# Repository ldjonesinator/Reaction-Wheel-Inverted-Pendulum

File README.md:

# Reaction Wheel Inverted Pendulum

## How it works
An inverted pendulum is an inherently unstable mechanical system because its centre of mass is positioned above its pivot point. As a result, small disturbances cause the pendulum to move away from its upright position unless corrected back to its original position. In this project, torque is produced by accelerating or decelerating a reaction wheel mounted to the pendulum. The resulting reaction torque acts on the pendulum body and is used to oppose its movement. 

The design uses an inertial measurement unit (IMU), to measure the pendulum’s angular position and motion. These measurements are processed by a Raspberry Pi Pico, which runs the feedback-control algorithm. The resulting control signal is supplied to an H-bridge motor driver, allowing the speed and direction of the brushed geared DC motor to be controlled. The motor drives the reaction wheel, completing the closed-loop control system. 

## How to use
You can refer to the documentation located in: [Instructions](Instructions.pdf)

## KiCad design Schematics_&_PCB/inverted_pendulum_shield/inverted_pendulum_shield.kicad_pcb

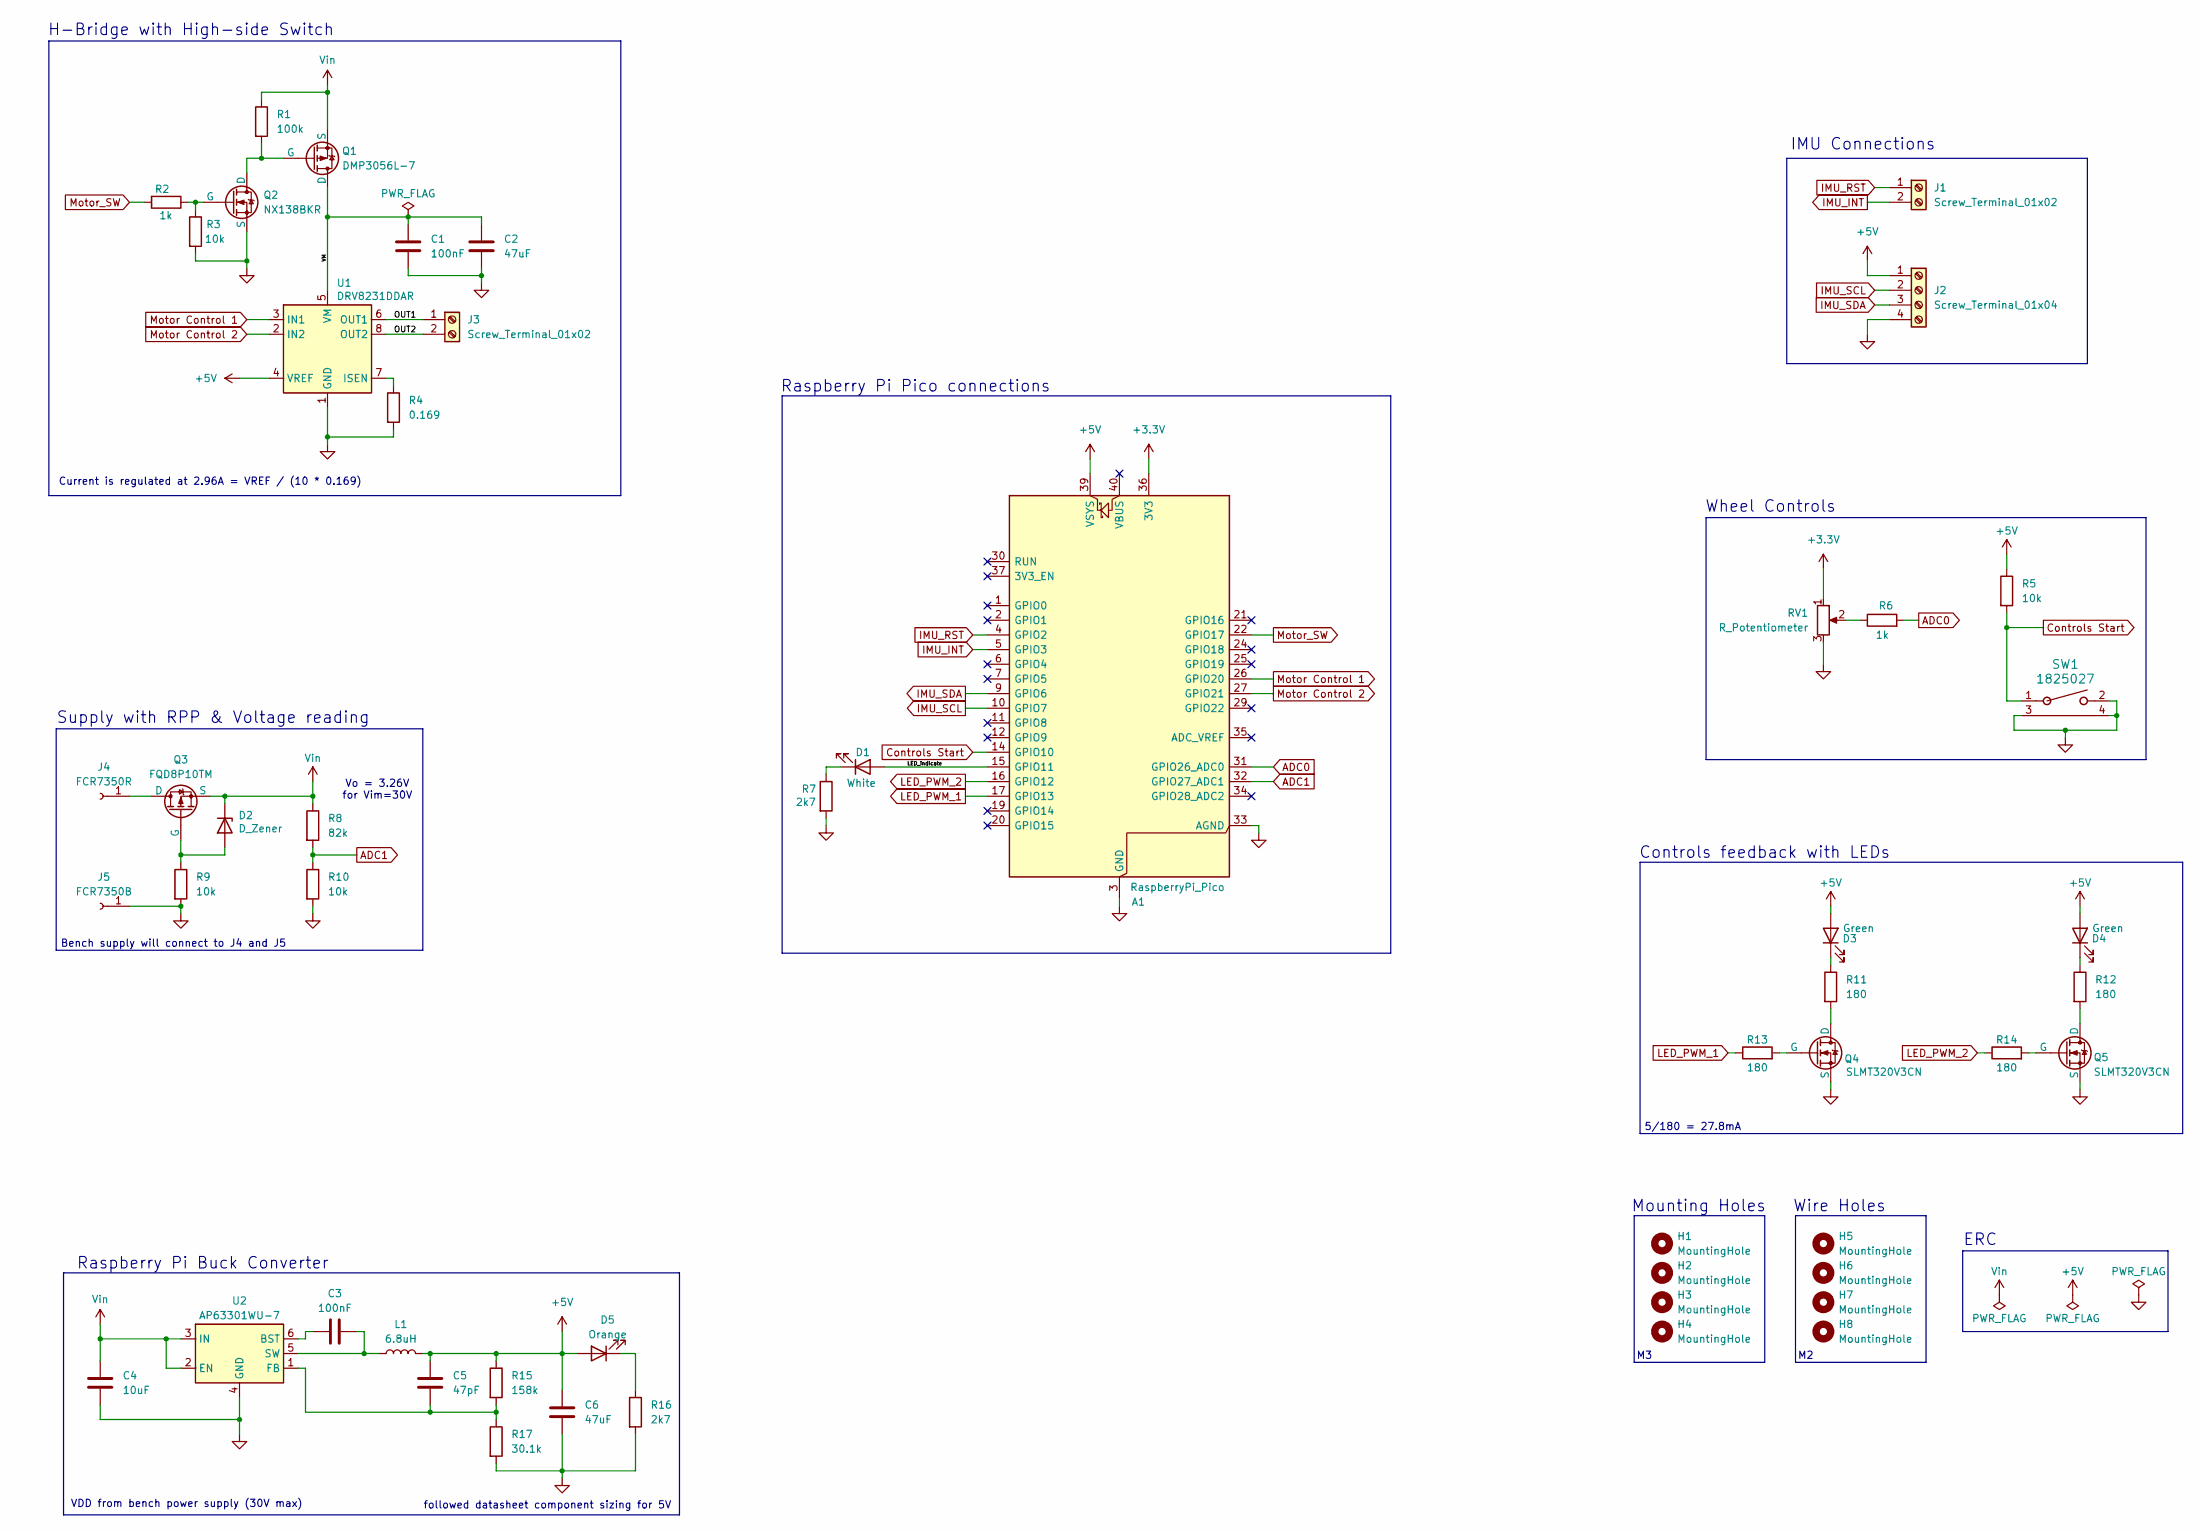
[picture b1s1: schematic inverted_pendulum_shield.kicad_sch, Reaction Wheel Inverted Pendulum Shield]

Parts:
A1: RaspberryPi_Pico; RaspberryPi_Pico_Common_THT
C1, C3: 100nF; C_0805_2012Metric
C2: 47uF; C_Radial_D5.0mm_H11.0mm_P2.00mm
C4: 10uF; C_0805_2012Metric
C5: 47pF; C_0603_1608Metric
C6: 47uF; C_0805_2012Metric
D1: White; LED_0603_1608Metric
D2: D_Zener; D_SOD-323
D3, D4: Green; LED_D10.0mm
D5: Orange; LED_0805_2012Metric
H1, H2, H3, H4, H5, H6, H7, H8: MountingHole; MountingHole_3.2mm_M3
J1, J3: Screw_Terminal_01x02; TerminalBlock_MaiXu_MX126-5.0-02P_1x02_P5.00mm
J2: Screw_Terminal_01x04; TerminalBlock_MaiXu_MX126-5.0-04P_1x04_P5.00mm
J4: FCR7350R; SolderWirePad_1x01_SMD_4x8mm
J5: FCR7350B; SolderWirePad_1x01_SMD_4x8mm
L1: 6.8uH; L_TDK_SLF7045
Q1: DMP3056L-7; SOT-23-3
Q2: NX138BKR; SOT-23
Q3: FQD8P10TM; TO-252-2
Q4, Q5: SLMT320V3CN; SOT-23
R1: 100k; R_0805_2012Metric
R2, R6: 1k; R_0805_2012Metric
R3, R5, R9, R10: 10k; R_0805_2012Metric
R4: 0.169; R_1206_3216Metric
R7, R16: 2k7; R_0805_2012Metric
R8: 82k; R_0805_2012Metric
R11, R12, R13, R14: 180; R_0805_2012Metric
R15: 158k; R_0805_2012Metric
R17: 30.1k; R_0805_2012Metric
RV1: R_Potentiometer; uc_potentiometer
SW1: 1825027; SW_THT_1825027-G_TEC
U1: DRV8231DDAR; Texas_HTSOP-8-1EP_3.9x4.9mm_P1.27mm_EP2.95x4.9mm_Mask2.4x3.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
U2: AP63301WU-7; TSOT-23-6

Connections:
+3.3V: A1.36 (3V3), RV1.1
+5V: A1.39 (VSYS), C5.1, C6.1, D3.2 (A), D4.2 (A), D5.2 (A), J2.1, L1.2, R5.1, R15.1, U1.4 (VREF)
/LED_indicate: A1.15 (GPIO11), D1.2 (A)
/OUT1: J3.1, U1.6 (OUT1)
/OUT2: J3.2, U1.8 (OUT2)
/VM: C1.1, C2.1, Q1.1 (D), U1.5 (VM)
ADC0: A1.31 (GPIO26_ADC0), R6.2
ADC1: A1.32 (GPIO27_ADC1), R8.2, R10.1
Controls Start: A1.14 (GPIO10), R5.2, SW1.1
GND: A1.3 (GND), A1.8 (GND), A1.13 (GND), A1.18 (GND), A1.23 (GND), A1.28 (GND), A1.33 (AGND), A1.38 (GND), C1.2, C2.2, C4.2, C6.2, J2.4, J5.1 (Pin_1_1), Q2.3 (S), Q4.3 (S), Q5.3 (S), R3.2, R4.2, R7.2, R9.2, R10.2, R16.2, R17.2, RV1.3, SW1.2, SW1.3, SW1.4, U1.1 (GND), U1.9 (GND), U2.4 (GND)
IMU_INT: A1.5 (GPIO3), J1.2
IMU_RST: A1.4 (GPIO2), J1.1
IMU_SCL: A1.10 (GPIO7), J2.2
IMU_SDA: A1.9 (GPIO6), J2.3
LED_PWM_1: A1.17 (GPIO13), R13.1
LED_PWM_2: A1.16 (GPIO12), R14.1
Motor Control 1: A1.26 (GPIO20), U1.3 (IN1)
Motor Control 2: A1.27 (GPIO21), U1.2 (IN2)
Motor_SW: A1.22 (GPIO17), R2.2
unnamed: D1.1 (K), R7.1
unnamed: D2.2 (A), Q3.2 (G), R9.1
unnamed: D3.1 (K), R11.1
unnamed: D4.1 (K), R12.1
unnamed: D5.1 (K), R16.1
unnamed: J4.1 (Pin_1_1), Q3.1 (D)
unnamed: Q1.2 (G), Q2.1 (D), R1.2
unnamed: Q2.2 (G), R2.1, R3.1
unnamed: Q4.1 (D), R11.2
unnamed: Q4.2 (G), R13.2
unnamed: Q5.1 (D), R12.2
unnamed: Q5.2 (G), R14.2
unnamed: R6.1, RV1.2
unnamed: R4.1, U1.7 (ISEN)
unnamed: C3.2, U2.6 (BST)
unnamed: C5.2, R15.2, R17.1, U2.1 (FB)
unnamed: C3.1, L1.1, U2.5 (SW)
Vin: C4.1, D2.1 (K), Q1.3 (S), Q3.3 (S), R1.1, R8.1, U2.2 (EN), U2.3 (IN)

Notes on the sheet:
Supply with RPP & Voltage reading
5/180 = 27.8mA
Current is regulated at 2.96A = VREF / (10 * 0.169)
followed datasheet component sizing for 5V
Wheel Controls
IMU Connections
H-Bridge with High-side Switch
Wire Holes
Controls feedback with LEDs
Raspberry Pi Buck Converter
Bench supply will connect to J4 and J5
Mounting Holes
ERC
Raspberry Pi Pico connections
Vo = 3.26V for Vim=30V
VDD from bench power supply (30V max)

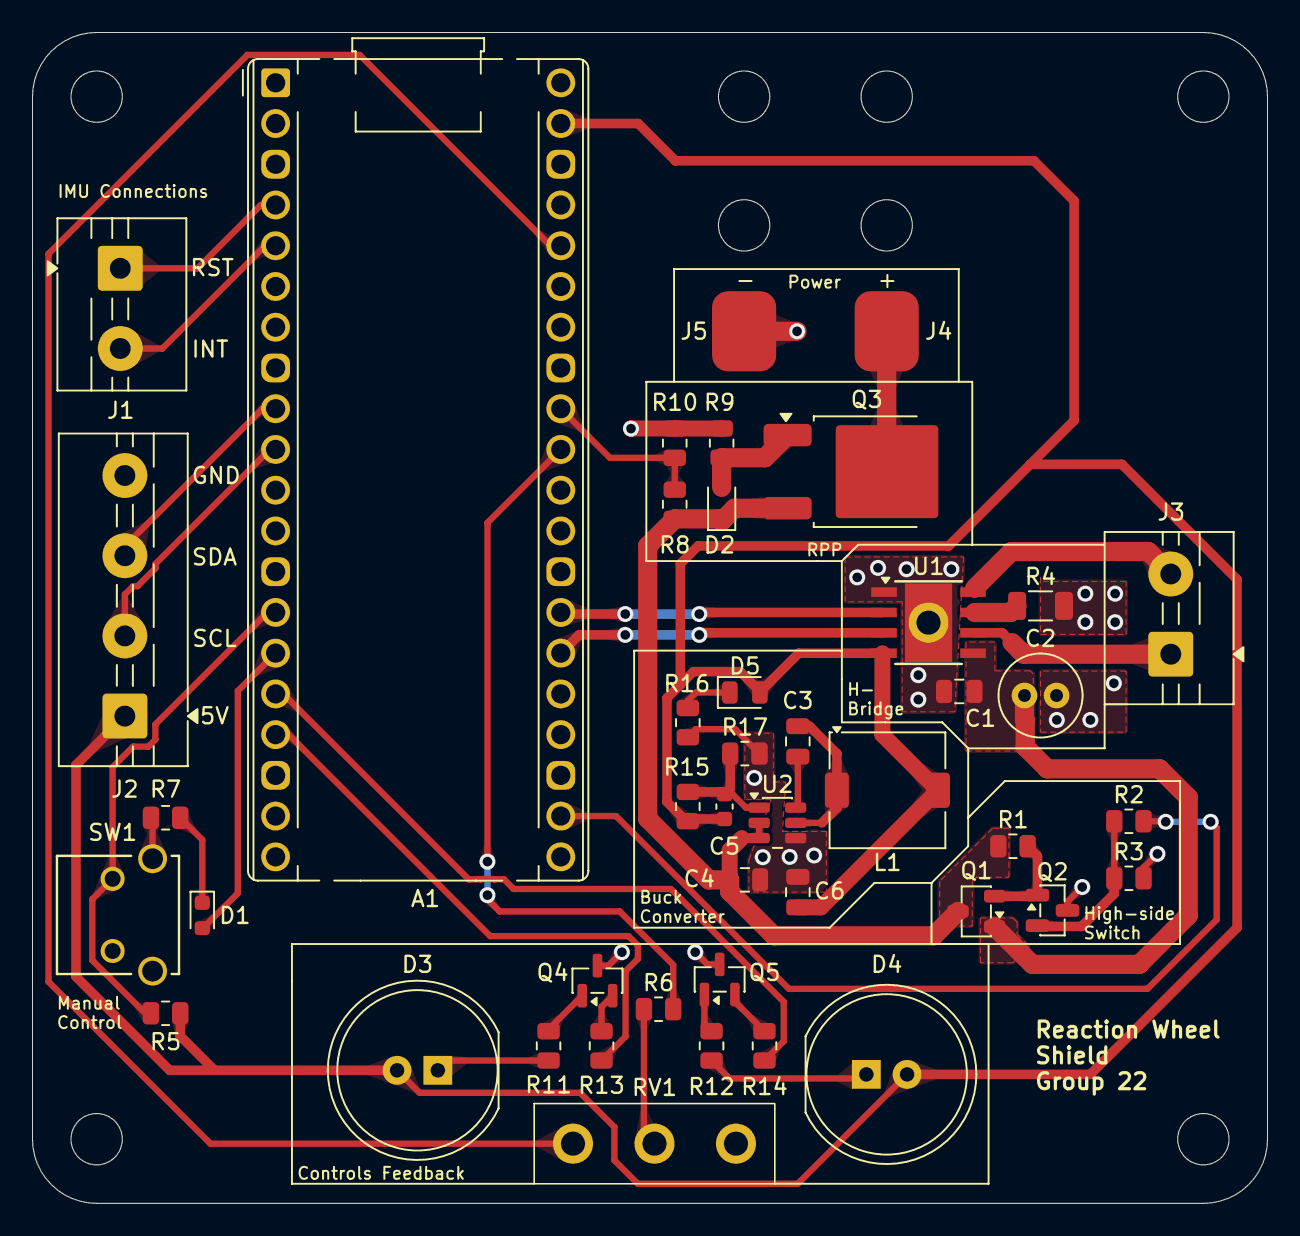
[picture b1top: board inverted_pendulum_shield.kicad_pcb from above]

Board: 2 copper layers, 77.0 x 73.0 mm, 52 parts (0 on the bottom side), 37 nets.
